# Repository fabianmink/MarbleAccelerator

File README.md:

# Marble Accelerator
This project deals with the construction of various accelerators (coil guns) for metallic marbles. It might be used e.g. for the GraviTrax marble run (marble data: $m = 8.6 \mathrm{g}$, $d = 12.7 \mathrm{mm}$). It has been used in various student projects in electrical engineering bachelor's and master's programs in the IEM department at the THM Friedberg, e.g. [this one](https://www.youtube.com/watch?v=bSArWLXCZdo) 

## Coilgun Designs

Coil winding cross sections are 15mm (coil length) x 7mm (inner radius 8mm, outer radius 15mm), leading to around 350 turns for 0.5mm wire diameter which results in an inductance of approximately 1mH.

### Horizontal coil design with two coils

Horizontal CAD design (base and tube parts)

The design is intended to be used with EVERLIGHT ITR9904 optical sensor for marble detection.

### Vertical coil design (single coil)

Vertical CAD design (base part and output)

The design is intended to be used with Vishay CNY70 optical sensor for marble detection.

The advantage of the vertical design is that the marble is at a defined state (no movement, $v_\mathrm{z} = 0$) at the beginning. This makes the accelerator parameters easier to tune, as the current level and duration of the current pulse are always the same.

## Coil winding
For an operating voltage of 24V, suitable wire diameters are in the range of 0.5mm ... 0.75mm.

## FEM Simulation (FEMM)

## Fitting of FEM results

The fit is based on the following coenergy equation:

- Co-Energy: $E_{\mathrm{Co}} = \frac{1}{2} \cdot L_\mathrm{min} \cdot I^2 \cdot \left[ 1 + d \cdot \exp \left( -0.5 \cdot \left(\frac{z - z_0}{z_\mathrm{s}}\right)^2 \right) \right]$

i.e.:

- z-Direction Force: $F_\mathrm{z} = \frac{\partial E_{\mathrm{Co}}}{\partial z} = - \frac{1}{2}  \cdot L_\mathrm{min} \cdot I^2 \cdot \left[ d \cdot \exp \left( -0.5 \cdot \left( \frac{z - z_0}{z_\mathrm{s}} \right)^2 \right) \right] \cdot \frac{z - z_0}{z^2_\mathrm{s}}$

- Flux Linkage: $\Psi = \frac{\partial E_{\mathrm{Co}}}{\partial I} = L_\mathrm{min} \cdot I \cdot \left[ 1 + d \cdot \exp \left( -0.5 \cdot \left( \frac{z - z_0}{z_\mathrm{s}} \right)^2 \right) \right]$

- Inductance: $L = \frac{\partial \Psi}{\partial I} = \frac{\partial^2 E_{\mathrm{Co}}}{\partial I^2} = L_\mathrm{min} \cdot \left[ 1 + d \cdot \exp \left( -0.5 \cdot \left( \frac{z - z_0}{z_\mathrm{s}} \right)^2 \right) \right]$

- Flux derivative: $\frac{\partial \Psi}{\partial z} = \frac{\partial^2 E_{\mathrm{Co}}}{\partial I \partial z} = - L_\mathrm{min} \cdot I \cdot \left[ d \cdot \exp \left( -0.5 \cdot \left( \frac{z - z_0}{z_\mathrm{s}} \right)^2 \right) \right] \cdot \frac{z - z_0}{z^2_\mathrm{s}}$ (needed for induced voltage calculation)

- Maximum force for given current occurs at the inflection points of $E_{\mathrm{Co}}$, i.e. at $z = z_0 \pm z_\mathrm{s}$: $F_\mathrm{z,max} \left( I \right)= \frac{1}{2}  \cdot L_\mathrm{min} \cdot I^2 \cdot d \cdot \exp \left( -0.5 \right) \cdot \frac{1}{z_\mathrm{s}}$

Resulting examplary fitted force:

## Dynamic System Simulation Model

The dynamic simulation implements the following equations:

- Velocity (z-direction): $\dot{v} = \frac{1}{m} \cdot F_\mathrm{z}$
- z-Position: $\dot{z} = v$
- Force calculation: $F_\mathrm{z} = F_\mathrm{z}\left(I, z\right)$ (see equation in chapter above)
- Coil current: $\dot{I} = \frac{1}{L \left(I, z\right) } \cdot \left[ u - R \cdot I - u_\mathrm{ind} \right]$
- Induced voltage: $u_\mathrm{ind} = \frac{\partial \Psi}{\partial z} \cdot v$

Model:

Coil electromagnetic subsystem:

## Power Electronics / Software

The software is designed for STM's B-G431B-ESC1 (Discovery kit with STM32G431CB MCU); it also includes the neccessary power MOSFETs. The supply voltage is 24V. An external capacitor of approximately 20mF is recommended in order to provide the high pulsed currents of 10..20A for durations of a few 10ms.

### Boost Converter

In case the coil should be battery-powered (e.g. from 3x AA alkaline cells / 4.5V), the boost converter board can be used.

### Hi-Side Switch

Can be used to power the coil.

## Simlar projects

- [lincoln1clarke (Instructables) - Electromagnetic Marble Accelerator for Gravitrax](https://www.instructables.com/Electromagnetic-Marble-Accelerator-for-Gravitrax/)
- [HyperspacePirate (Thingiverse) - Electromagnetic Accelerator](https://www.thingiverse.com/thing:4918703)
- [William Le - Perpetual Marble Machine](https://lovelywings.store/)

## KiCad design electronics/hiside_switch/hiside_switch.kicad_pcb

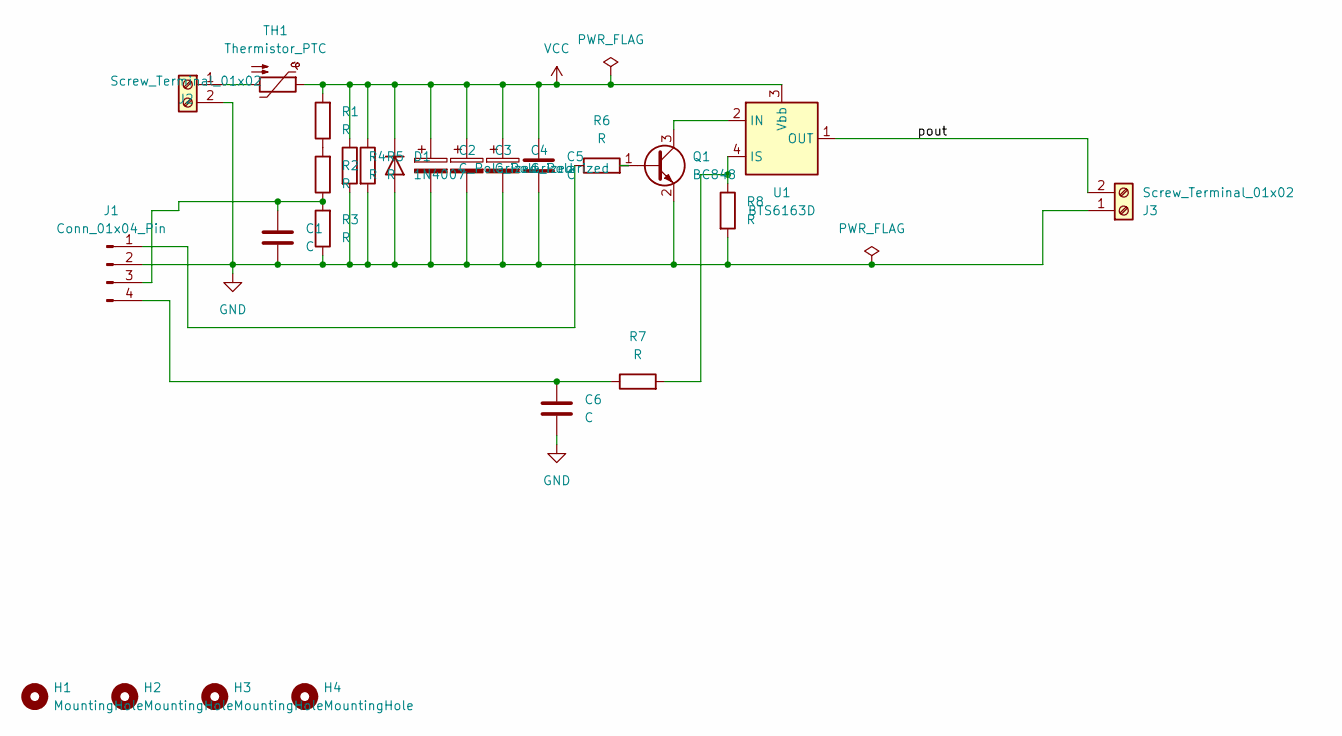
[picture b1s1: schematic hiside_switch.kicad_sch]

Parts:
C1, C6: C; C_0805_2012Metric_Pad1.18x1.45mm_HandSolder
C2, C3, C4: C_Polarized; CP_Radial_D26.0mm_P10.00mm_SnapIn
C5: C; C_Rect_L7.2mm_W4.5mm_P5.00mm_FKS2_FKP2_MKS2_MKP2
D1: 1N4007; D_DO-41_SOD81_P10.16mm_Horizontal
H1, H2, H3, H4: MountingHole; MountingHole_3.2mm_M3
J1: Conn_01x04_Pin; PinHeader_1x04_P2.54mm_Vertical
J2, J3: Screw_Terminal_01x02; TerminalBlock_Phoenix_MKDS-1,5-2-5.08_1x02_P5.08mm_Horizont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
Q1: BC848; SOT-23
R1, R2, R3, R6, R7, R8: R; R_0805_2012Metric_Pad1.20x1.40mm_HandSolder
R4, R5: R; R_Axial_DIN0309_L9.0mm_D3.2mm_P12.70mm_Horizontal
TH1: Thermistor_PTC; RV_Disc_D9mm_W3.3mm_P5mm
U1: BTS6163D; TO-252-4

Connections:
/pout: J3.2, U1.1 (OUT), U1.5 (OUT)
GND: C1.2, C2.2, C3.2, C4.2, C5.2, C6.2, D1.2 (A), J1.2, J2.2, J3.1, Q1.2 (E), R3.1, R4.2, R5.2, R8.2
unnamed: J1.1, R6.1
unnamed: C1.1, J1.3, R2.1, R3.2
unnamed: C6.1, J1.4, R7.1
unnamed: J2.1, TH1.2
unnamed: Q1.1 (B), R6.2
unnamed: Q1.3 (C), U1.2 (IN)
unnamed: R1.1, R2.2
unnamed: R7.2, R8.1, U1.4 (IS)
VCC: C2.1, C3.1, C4.1, C5.1, D1.1 (K), R1.2, R4.1, R5.1, TH1.1, U1.3 (Vbb)

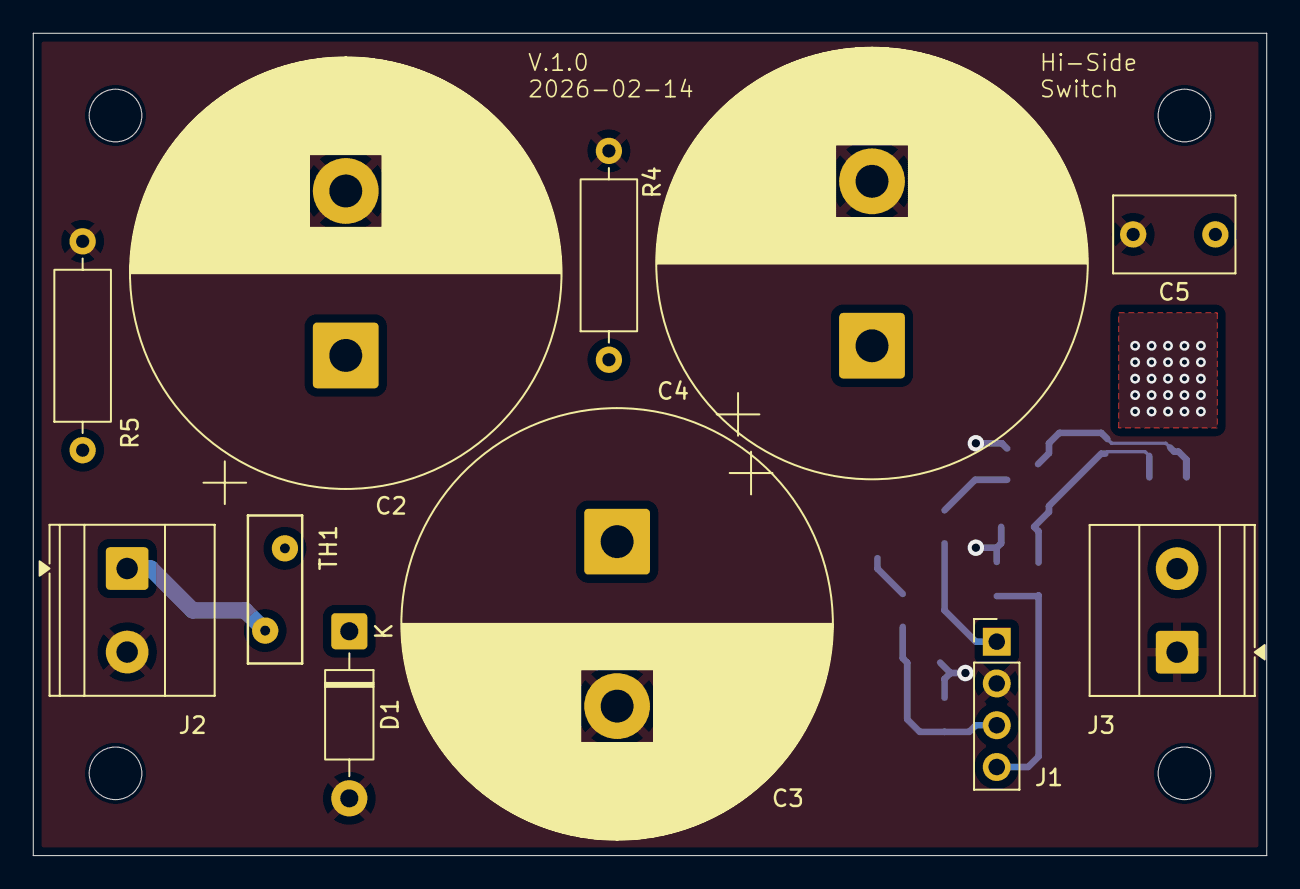
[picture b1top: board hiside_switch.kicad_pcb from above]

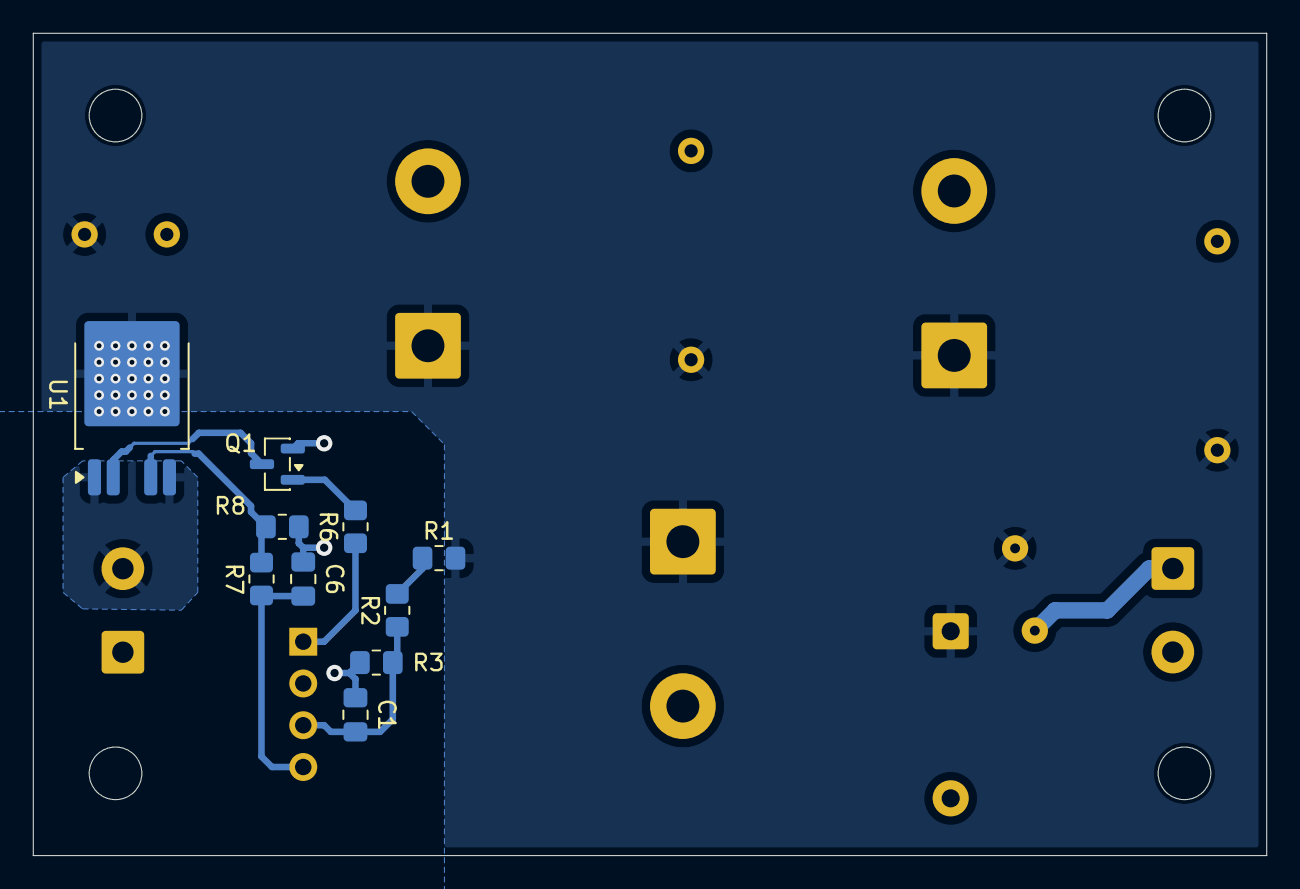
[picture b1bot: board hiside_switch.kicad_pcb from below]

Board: 2 copper layers, 75.0 x 50.0 mm, 25 parts (10 on the bottom side), 11 nets.

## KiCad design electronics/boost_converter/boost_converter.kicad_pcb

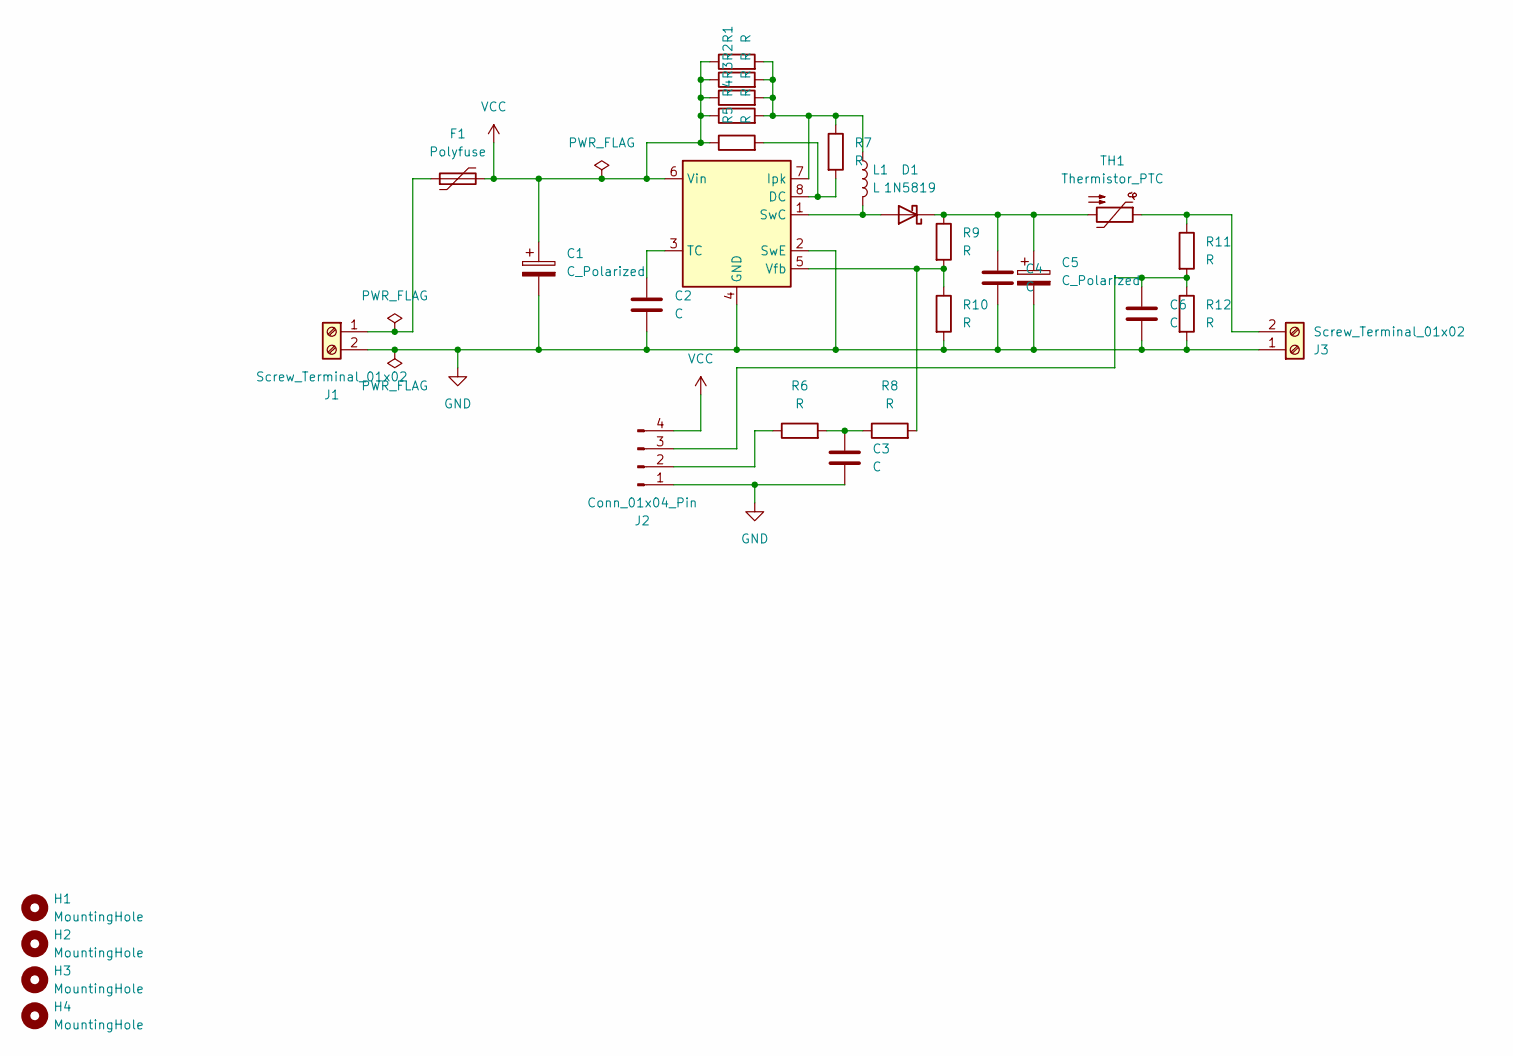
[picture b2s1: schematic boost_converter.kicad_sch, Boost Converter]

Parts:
C1: C_Polarized; CP_Radial_D10.0mm_P2.50mm_P5.00mm
C2: C; C_Disc_D3.0mm_W2.0mm_P2.50mm
C3, C6: C; C_Rect_L4.6mm_W3.8mm_P2.50mm_MKS02_FKP02
C4: C; C_Rect_L4.6mm_W4.6mm_P2.50mm_MKS02_FKP02
C5: C_Polarized; CP_Radial_D10.0mm_P5.00mm_P7.50mm
D1: 1N5819; D_DO-41_SOD81_P10.16mm_Horizontal
F1: Polyfuse; Fuse_BelFuse_0ZRE0005FF_L8.3mm_W3.8mm
H1, H2, H3, H4: MountingHole; MountingHole_3.2mm_M3
J1, J3: Screw_Terminal_01x02; TerminalBlock_Phoenix_MKDS-1,5-2-5.08_1x02_P5.08mm_Horizont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
J2: Conn_01x04_Pin; PinHeader_1x04_P2.54mm_Vertical
L1: L; L_Radial_D10.0mm_P5.00mm_Fastron_07P
R1, R2, R3, R4, R5, R6, R7, R8, R9, R10, R11, R12: R; R_Axial_DIN0207_L6.3mm_D2.5mm_P10.16mm_Horizontal
TH1: Thermistor_PTC; RV_Disc_D9mm_W3.3mm_P5mm
U1: MC34063AP; DIP-8_W7.62mm

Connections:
GND: C1.2, C2.2, C3.2, C4.2, C5.2, C6.2, J1.2, J2.1, J3.1, R10.2, R12.2, U1.2 (SwE), U1.4 (GND)
unnamed: C3.1, R6.2, R8.1
unnamed: D1.2 (A), L1.2, U1.1 (SwC)
unnamed: C4.1, C5.1, D1.1 (K), R9.1, TH1.2
unnamed: F1.1, J1.1
unnamed: J2.2, R6.1
unnamed: C6.1, J2.3, R11.2, R12.1
unnamed: J3.2, R11.1, TH1.1
unnamed: R5.2, R7.2, U1.8 (DC)
unnamed: L1.1, R1.2, R2.2, R3.2, R4.2, R7.1, U1.7 (Ipk)
unnamed: C2.1, U1.3 (TC)
unnamed: R8.2, R9.2, R10.1, U1.5 (Vfb)
VCC: C1.1, F1.2, J2.4, R1.1, R2.1, R3.1, R4.1, R5.1, U1.6 (Vin)

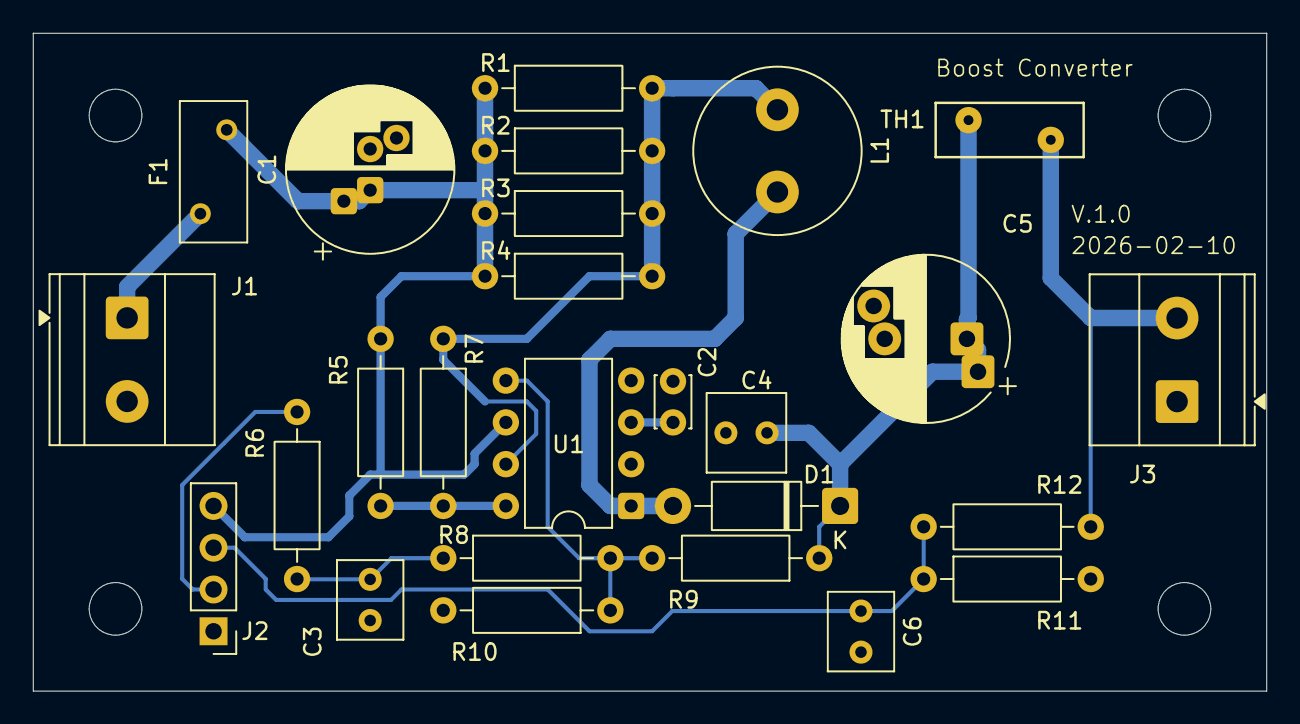
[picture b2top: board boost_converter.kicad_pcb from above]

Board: 2 copper layers, 75.0 x 40.0 mm, 30 parts (0 on the bottom side), 13 nets.

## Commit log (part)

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2022-04-08 initial revision
2022-04-08 Readme images added
2022-06-14 autostart; clean up code
2022-06-14 Light Sensor added Update to latest Cube version
2022-06-15 timing adapted; auto-quit errors
2022-06-23 sensor triggering improved
2022-06-23 new version with two seperate coils
2022-09-14 Magnetic Energy added; Plot of Energy and Coenergy
2023-01-12 file for single coil added
2023-01-13 only half position range due to symmetry, plotting over position and current
2023-01-13 grid data
2023-01-18 Coil / Marble flipped in code
2023-04-10 Can interface implemented for testing
2023-04-11 data added to CAN CAN TX successfully tested
2023-04-17 32kHz PWM, 16kHz control
2023-04-18 16kHz PWM corrected and verified
2023-04-18 files added
2023-04-18 timing / current adapted to working values; CAN data reduced
2023-04-18 CAN: back to 1ms cycle / always sent data
2023-05-04 controller gain reduction
2023-05-04 new FEMM model for "V2a" accelerator model; inductance calculation
2023-05-17 Powerstage dead time increased to 1us
2025-03-12 cad files added
2025-03-15 FEMM and result evaluation updated; data fitting to parametric function
2025-03-15 axis labels added
2025-03-15 remove of old data
2025-03-15 images updated to latest design
2025-03-15 geometry optimized
2025-03-15 winding assistant added stl files added
2025-03-17 nominal pocket size increased due to printing tolerances
2025-03-20 coil analytical calculation according to Wheeler's formula
2025-03-20 units and plots improved
2025-03-20 re-calculation / simulation for 0.5mm wire diameter
2025-03-20 variables renamed
2025-03-20 simulation added
2025-03-20 simulation simplified / image added
2025-03-21 new "vertical" design (not tested yet)
2025-03-21 runway holder improved
2025-03-22 height corrected, sensor hole stop added, wire holes added
2025-03-23 vertical Accelerator implemented
2025-03-23 timing adjusted
2025-03-23 Coenergy fit equation added
2025-03-23 headings added
2025-03-23 headings corrected
2025-03-24 Project rename; equations for dynamic simulation added
2025-03-24 equations explained
2025-03-24 whitespace removed
2025-03-24 more equation explanation
2025-03-24 position equation corrected
2025-03-24 tried to get equation right so that github page shows it correctly
2025-03-24 another try for velocity equation
2025-03-24 try whether index works
2025-03-24 velocity equation improved: index does not work for "dotted" variable in github
2025-03-24 CAD files screenshots added
2025-03-24 coil subsystem added
2025-03-24 new fotos added for vertical design
2025-03-24 project rename
2025-03-24 project rename part 2
2025-03-24 unneccessary files remove d
2025-03-24 non-autogenerated code moved to separate "control" files
2025-03-24 comment corrected
2025-03-24 controller functions moved to separate files
2025-03-24 code rework and cleanup
2025-03-24 advantage of vertical design
2025-03-24 0.5mm Ramp added to runway
2025-03-25 height adjusted; bottom hole for coil winding machine fixation; detector hole optimized
2025-03-25 winding assistant added
2025-03-26 Mounting holes added
2025-03-26 horizontal design files moved to subfolder
2025-03-26 output tube added
2025-03-26 output
2025-03-26 output for vertical coil optimized
2025-03-26 timing corrected (max PWM values); code cleanup an rework
2025-03-26 commands for start / stop implemented
2025-03-26 integer number formats optimized
2025-03-26 voltage limitation / controller parameters optimized
2025-03-27 controller parameters integer arithmetics optimzed
2025-03-27 output voltages symmetrized
2025-03-29 remove of unnecessary defines
2025-03-29 manual triggering vcon mode prepared for implementation single coil design variant prepared for implementation
2025-03-29 current setpoint generation moved to sensor_calculation; output voltage calculation corrected
2025-03-29 documentation rework / new images / qrcode
2025-03-29 hole diameter increase to 10mm due to winding machine shaft diameter
2025-03-30 plot of FEM simulated data using python
2025-03-30 perform curve fitting
2025-03-30 magnetics model functions optimized
2025-03-30 different plot types
2025-03-30 2d plot types
2025-03-31 brackets added correctly
2025-03-31 coil dimensions changed to latest vertical design
2025-03-31 Coenergy formulas modified by factor 0.5 within exponential to have Gaussian function with sigma=zs; matlab plotting functions removed
2025-03-31 cdots added
2025-03-31 force fitting example from python instead of matlab
2025-04-01 max force calculation and plotting
2025-04-03 coil winding image added
2025-04-05 model with capacitor / high-side switch added
2025-04-06 fem calculation for variation of both ia and ib
2025-04-06 uart enabled and test string sending
2025-04-07 send data from datarecorder via uart
2025-04-07 data recorder: auto trigger, adding more values, increase uart baudrate
2025-04-07 serial data read via python (simple test only)
2025-04-08 plot updating correctly
2025-04-08 grid / axis labels
2025-04-08 singlecoil design parameters implemented
2025-04-11 tech drawings improved / updated
2025-04-11 hight dimension added to techdraw
2025-04-11 cable output added
2025-04-12 formatting
2025-04-12 current calculation for high positive values of duty cycle
2025-04-14 exception handling
2025-04-14 wrong current measurement phase b workaround
2025-04-14 current references added to datarec
2025-04-14 test of new profile generator
2025-04-14 wrong references corrected, parameters tuned; now working for single coil design
2025-04-14 implementation for two-coil design also working now
2025-04-14 exception handling improved
2025-04-14 shorter wait time for next marble
2025-05-05 simple single coil simulation added
2025-05-06 additional holes for coil wire
2025-05-06 Parameters for new coil design with n=180 windings
2025-05-06 optional 2nd COM interface
2025-05-13 controller baseplate added
2025-05-13 connectors + holders
2025-05-13 tech draw added
2025-05-13 holder for stepup converter removed; clamp rails added
2025-05-15 mount for wago cage clamp
2025-09-22 test for webserver added
2025-09-22 year corrected ;-)
2025-09-22 raw string literal
2025-12-06 electronic components list added
2025-12-06 calculations added
2025-12-07 components list updated / general calculations added
2025-12-13 voltage divider calc optimized
2025-12-22 stepup converter design added
2025-12-22 alternative output voltage design with 'uncontrolled' voltage
2026-01-27 extensionTube added
2026-01-27 variable height; 70mm varian stl added
2026-02-05 controller for vertical coil added
2026-02-05 ADC enabled (not tested)
2026-02-06 injected conversion added
2026-02-06 read only injected channels
2026-02-06 capacitor voltage controller implemented; pulse generation optimized
2026-02-06 additional calculation for voltage
2026-02-06 auto-active; parameters changed
2026-02-08 boost converter KiCAD project added
2026-02-08 boost converter image added
2026-02-10 silk screen optimized; drc ok
2026-02-10 Labels added; ready for production
2026-02-11 board carrier for electronics added
2026-02-12 hi side switch pcb draft added
2026-02-14 routing completed
2026-02-14 hiside switch added
2026-02-14 hiside switch img added
2026-02-14 hi side switch board mounting and controller board pad added
2026-02-16 sketch and hole naming
2026-02-16 output catcher added
2026-02-16 tower added
2026-02-16 tower completed; pin added
2026-02-16 stls added
2026-02-17 height parametrized
2026-02-17 fixation pin diameter corrected; stl updated
2026-02-17 mounting hole diameter increased to 3.2mm
2026-02-18 height increased; inlet hole on all sides
2026-02-18 Mounting hole size increased from 3.0mm to 3.2mm; wire hole position optimized
2026-02-19 Stability optimized
2026-02-21 Fixation hole Diameter and Depth increased
2026-02-21 housing finished
2026-02-24 USB connector pocket optimized
2026-03-19 min Cap voltage must be reached before pulse start
2026-03-19 voltage must be in range for specified amount of time
2026-04-15 drawing name changed; pdf export
2026-04-15 runway path inclination increased
2026-04-15 "open" variant for vertical accelerator added
2026-04-16 coil runway removed; additional coil without top
2026-04-17 chamfers added
2026-04-18 extract and plot point values
2026-04-18 plots improved
2026-04-18 zm position variable
2026-04-19 geometry creation moved to separate file / function
2026-04-19 resolution reduced, individual filename
2026-04-21 calc in a loop
2026-04-21 loop calculation and plotting
2026-04-22 housing for hi-side switch board only added
2026-04-24 TechDraw / 3D View added
2026-04-26 Baseplate added
2026-04-26 fillet added
2026-04-27 outer dimensions adjusted für Auer eurobox
2026-05-04 drawings
2026-05-04 rename baseplate
2026-05-04 Baseplate with variable cell diameter added (e.g. for tuning to laser beam width)
2026-05-19 Version for steel filling added
2026-05-19 support
2026-05-20 Top of filling pocket optimized
2026-05-20 inner geometry optimzed
2026-05-20 magnetHolder added
2026-05-20 length increased
2026-05-21 transparent mode enabled
2026-05-22 stick length decreased by 1mm
2026-05-24 transparent
2026-05-24 winding added
2026-06-03 final optimal cell width 29.5mm
